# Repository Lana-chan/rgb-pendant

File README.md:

RGB Pendant
===========

These are the source files (schematic and code) for a color-changing trinket, originally designed to be used as a necklace pendant.
The design is based off an ATtiny85 and a generic common-cathode RGB LED.

The boards have been done in EAGLE 7.1.0 Light and KiCad (2013-07-07BZR 4022)-stable and as of this commit have not yet been tested for manufacture, but they have no design-rule errors.
To compile the code with the Arduino IDE, you need the following:
* ATtiny cores: https://code.google.com/p/arduino-tiny/
* WinAVR Linker bugfix: http://forum.arduino.cc/index.php/topic,116674.0.html

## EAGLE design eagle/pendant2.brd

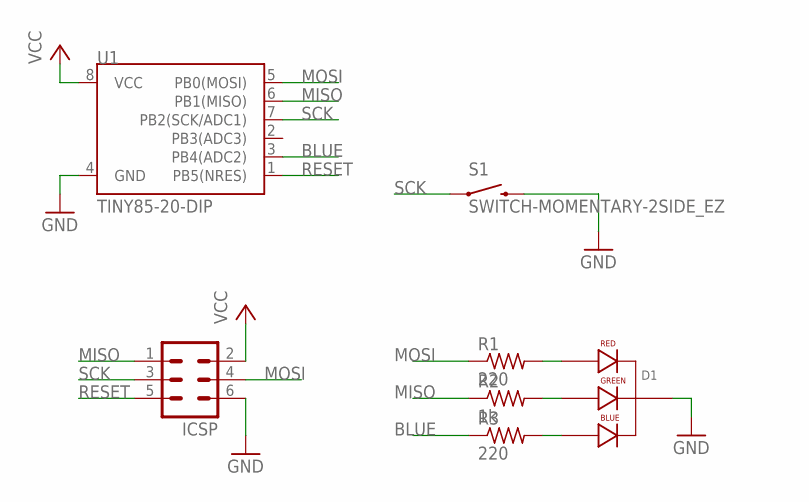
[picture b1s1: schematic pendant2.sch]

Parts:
D1: LED-RGB-CC-THRUCLEAR; LED-RGB-THRU
ICSP: MA03-2
R1, R3: 220; 0207/2V
R2: 1k; 0207/2V
S1: SWITCH-MOMENTARY-2SIDE_EZ; TACTILE-PTH-SIDEEZ
U1: TINY85-20-DIP; DIP08

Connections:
BLUE: R3.1, U1.3 (PB4(ADC2))
GND: D1.2 (CATHODE), ICSP.6, S1.2, U1.4 (GND)
MISO: ICSP.1, R2.1, U1.6 (PB1(MISO))
MOSI: ICSP.4, R1.1, U1.5 (PB0(MOSI))
unnamed: D1.1 (RED_CATHODE), R1.2
unnamed: D1.3 (GREEN_CATHODE), R2.2
unnamed: D1.4 (BLUE_CATHODE), R3.2
RESET: ICSP.5, U1.1 (PB5(NRES))
SCK: ICSP.3, S1.1, U1.7 (PB2(SCK/ADC1))
VCC: ICSP.2, U1.8 (VCC)

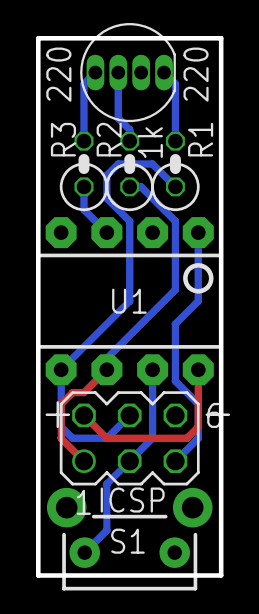
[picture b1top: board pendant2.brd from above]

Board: 2 copper layers, 10.2 x 29.8 mm, 7 parts (0 on the bottom side), 10 nets.

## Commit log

2014-10-26 ATtiny85-powered color-changing pendant
    These are the source files (schematic and code) for a color-changing
    trinket, originally designed to be used as a necklace pendant.
2014-10-26 Board slightly reduced in size, silkscreen improved
2014-10-27 Made the board yet smaller
2014-10-27 fixed back silkscreen
2014-10-27 replacing ATtiny part with SparkFun version for standardizing
2014-10-27 thicker routes
2014-11-09 redone routes and replaced resistor type
2014-11-09 created kicad version of the board
2014-12-08 silkscreen improvement
2014-12-11 fixing ICSP header
2016-06-12 case fix

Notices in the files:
parts and their libraries:
SparkFun-LED: Licensing: Creative Commons ShareAlike 4.0 International - https://creativecommons.org/licenses/by-sa/4.0
